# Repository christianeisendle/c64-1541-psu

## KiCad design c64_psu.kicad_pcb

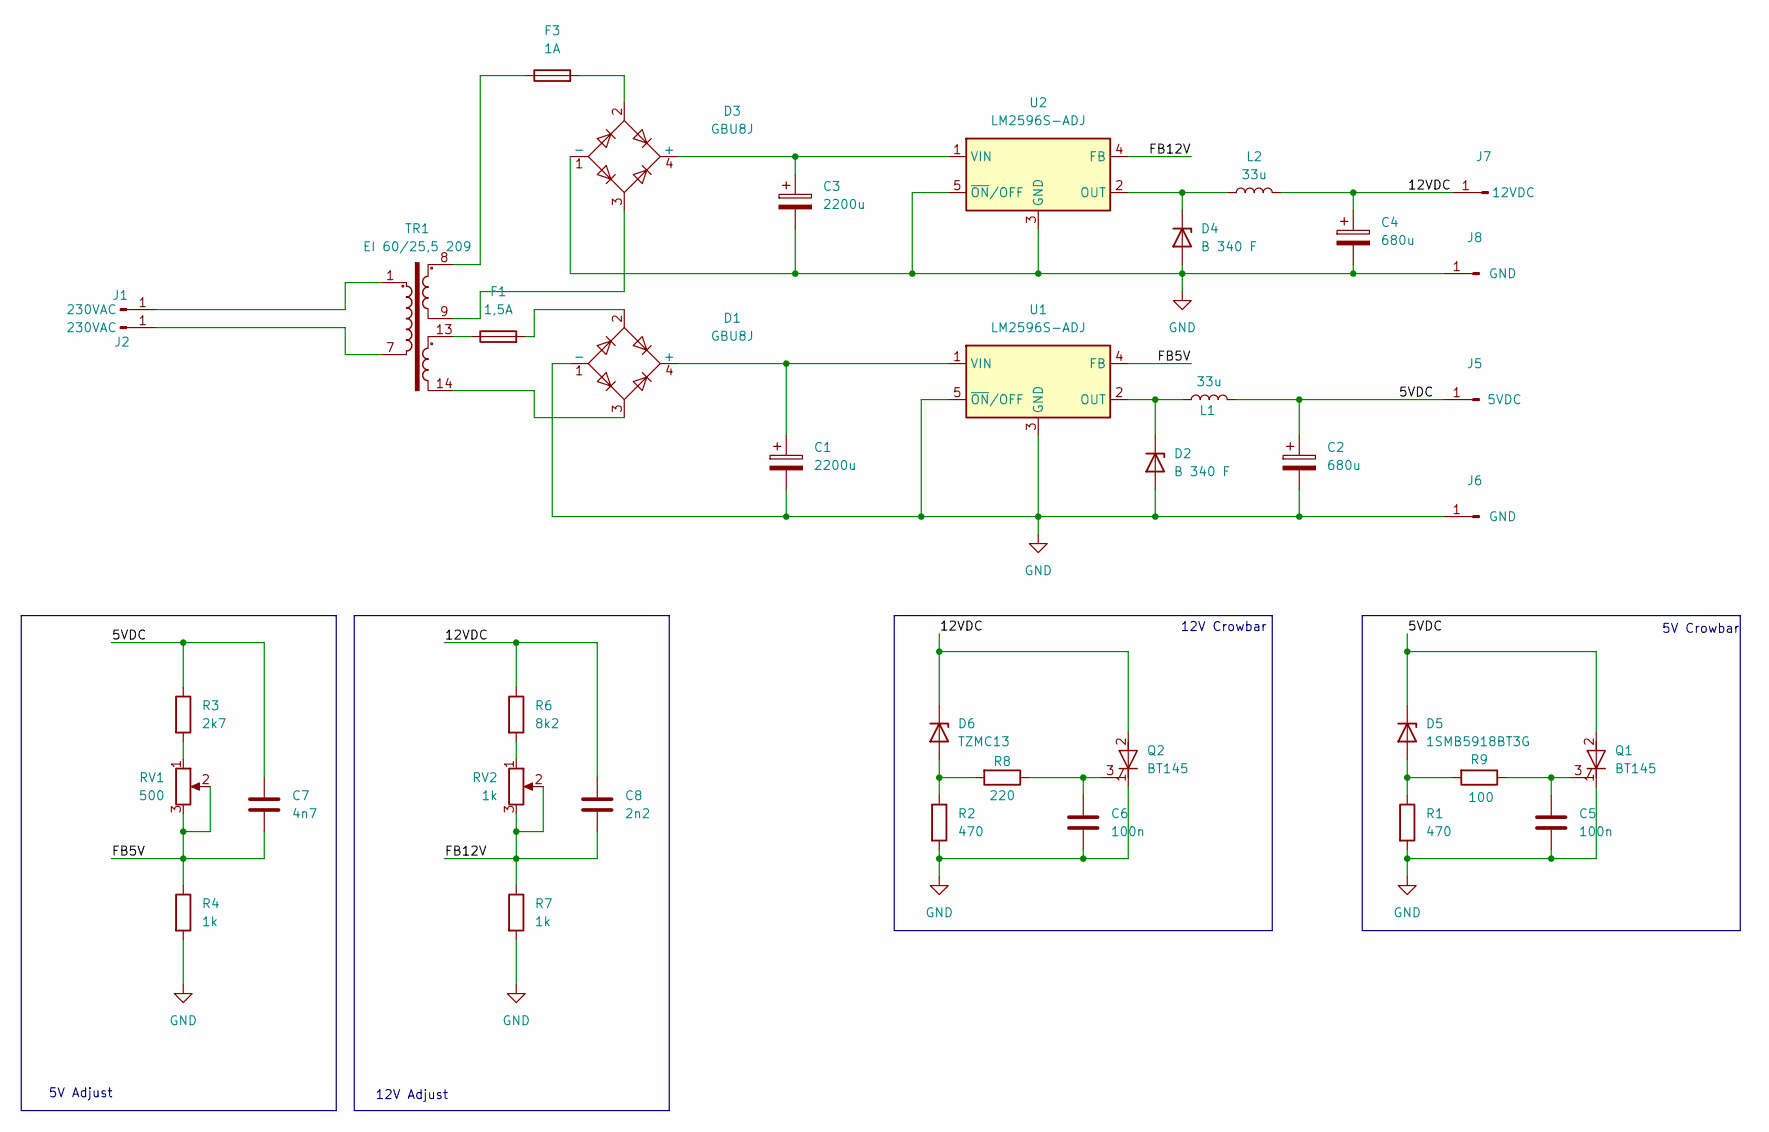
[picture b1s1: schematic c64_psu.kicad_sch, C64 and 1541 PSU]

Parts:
C1, C3: 2200u; CP_Radial_D12.5mm_P5.00mm
C2, C4: 680u; CP_Radial_D10.0mm_P5.00mm
C5, C6: 100n; C_0402_1005Metric_Pad0.74x0.62mm_HandSolder
C7: 4n7; C_0402_1005Metric_Pad0.74x0.62mm_HandSolder
C8: 2n2; C_0402_1005Metric_Pad0.74x0.62mm_HandSolder
D1, D3: GBU8J; Diode_Bridge_Vishay_GBU
D2, D4: B 340 F; D_SMC
D5: 1SMB5918BT3G; D_SMB
D6: TZMC13; D_MiniMELF
F1: 1,5A; Fuseholder_Clip-5x20mm_Schurter_CQM_Inline_P20.60x5.00mm_D1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
F3: 1A; Fuseholder_Clip-5x20mm_Schurter_CQM_Inline_P20.60x5.00mm_D1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
J1, J2: 230VAC; TestPoint_THTPad_4.0x4.0mm_Drill2.0mm
J5: 5VDC; TestPoint_THTPad_4.0x4.0mm_Drill2.0mm
J6, J8: GND; TestPoint_THTPad_4.0x4.0mm_Drill2.0mm
J7: 12VDC; TestPoint_THTPad_4.0x4.0mm_Drill2.0mm
L1, L2: 33u; L_Radial_D12.5mm_P7.00mm_Fastron_09HCP
Q1, Q2: BT145; TO-220-3_Vertical
R1, R2: 470; R_0402_1005Metric_Pad0.72x0.64mm_HandSolder
R3: 2k7; R_0402_1005Metric_Pad0.72x0.64mm_HandSolder
R4, R7: 1k; R_0402_1005Metric_Pad0.72x0.64mm_HandSolder
R6: 8k2; R_0402_1005Metric_Pad0.72x0.64mm_HandSolder
R8: 220; R_0402_1005Metric_Pad0.72x0.64mm_HandSolder
R9: 100; R_0402_1005Metric_Pad0.72x0.64mm_HandSolder
RV1: 500; Potentiometer_Bourns_3296W_Vertical
RV2: 1k; Potentiometer_Bourns_3296W_Vertical
TR1: EI 60/25,5 209; Transformer_EI_60_25,5_209
U1, U2: LM2596S-ADJ; TO-263-5_TabPin3

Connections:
/5VDC: C2.1, C7.1, D5.1 (K), J5.1, L1.2, Q1.2 (A), R3.1
/12VDC: C4.1, C8.1, D6.1 (K), J7.1, L2.2, Q2.2 (A), R6.1
/FB5V: C7.2, R4.1, RV1.2, RV1.3, U1.4 (FB)
/FB12V: C8.2, R7.1, RV2.2, RV2.3, U2.4 (FB)
GND: C1.2, C2.2, C3.2, C4.2, C5.2, C6.2, D1.1 (-), D2.2 (A), D3.1 (-), D4.2 (A), J6.1, J8.1, Q1.1 (K), Q2.1 (K), R1.2, R2.2, R4.2, R7.2, U1.3 (GND), U1.5 (~ON/OFF), U2.3 (GND), U2.5 (~ON/OFF)
unnamed: C1.1, D1.4 (+), U1.1 (VIN)
unnamed: D1.2, F1.2
unnamed: D1.3, TR1.14
unnamed: D2.1 (K), L1.1, U1.2 (OUT)
unnamed: C3.1, D3.4 (+), U2.1 (VIN)
unnamed: D3.2, F3.2
unnamed: D3.3, TR1.9
unnamed: D4.1 (K), L2.1, U2.2 (OUT)
unnamed: D5.2 (A), R1.1, R9.2
unnamed: D6.2 (A), R2.1, R8.2
unnamed: F1.1, TR1.13
unnamed: F3.1, TR1.8
unnamed: J1.1, TR1.1
unnamed: J2.1, TR1.7
unnamed: C5.1, Q1.3 (G), R9.1
unnamed: C6.1, Q2.3 (G), R8.1
unnamed: R3.2, RV1.1
unnamed: R6.2, RV2.1

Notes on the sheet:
12V Adjust
5V Crowbar
12V Crowbar
5V Adjust

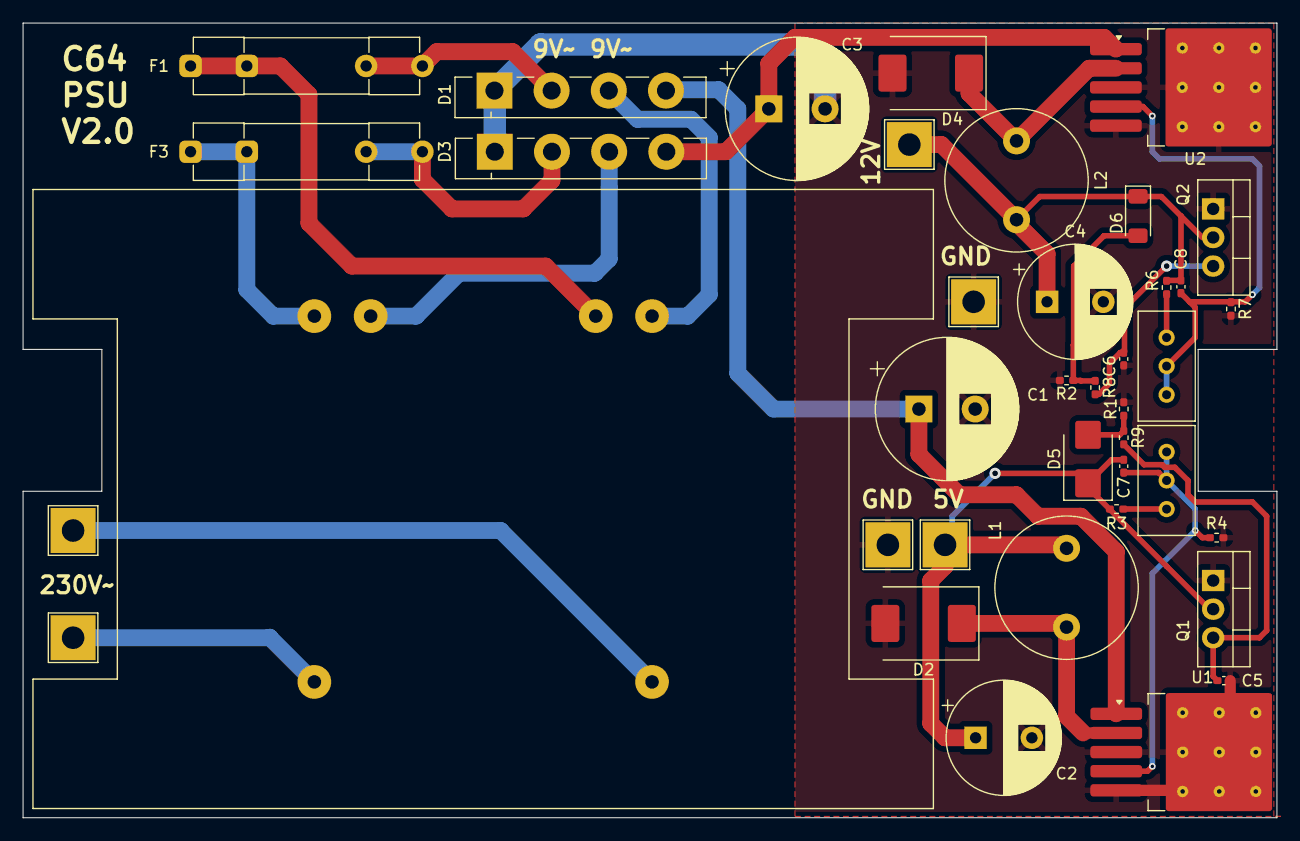
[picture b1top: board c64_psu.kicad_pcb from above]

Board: 2 copper layers, 111.4 x 70.6 mm, 39 parts (0 on the bottom side), 23 nets.

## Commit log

2025-01-11 Initial commit - v1.0
2025-02-07 v2.0: Replace LM2596 with SMD type
